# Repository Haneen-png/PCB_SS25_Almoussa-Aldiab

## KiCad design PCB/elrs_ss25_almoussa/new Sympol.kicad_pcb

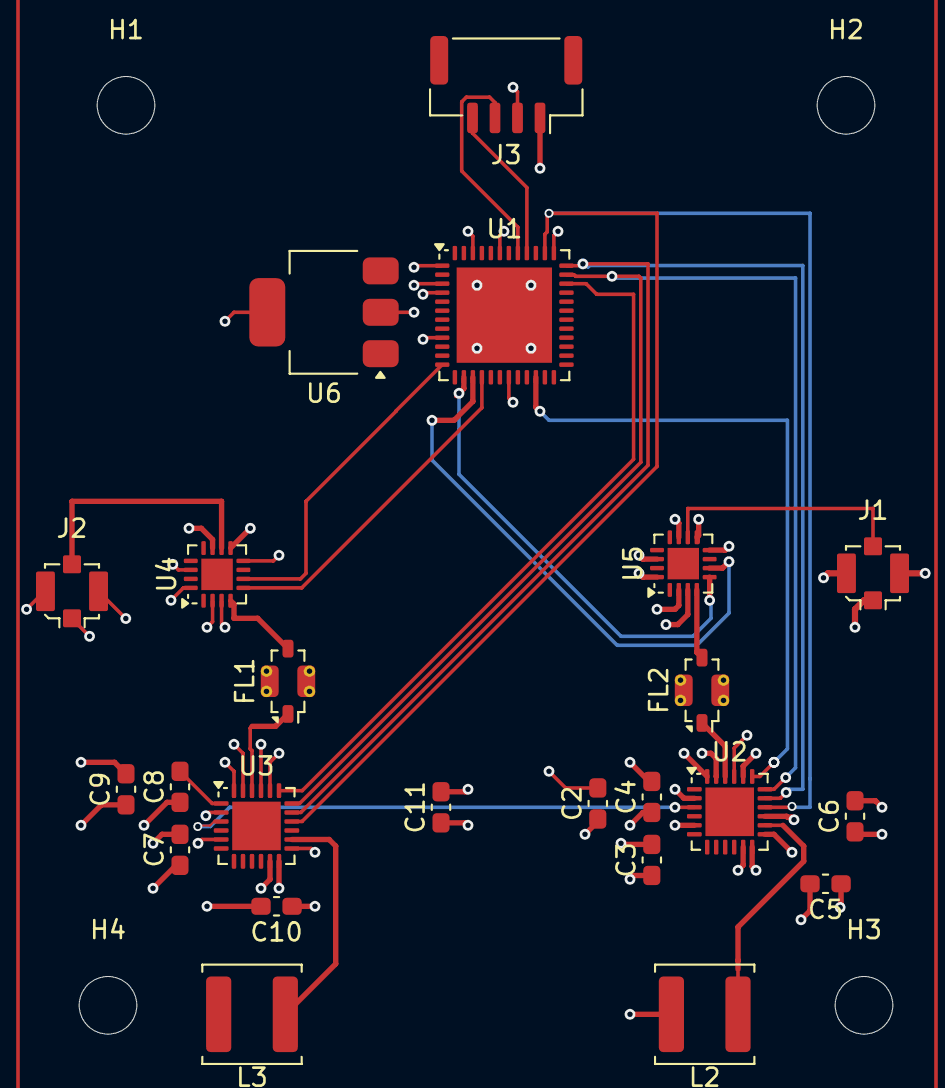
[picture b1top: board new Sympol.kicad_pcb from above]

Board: 4 copper layers, 27 parts (0 on the bottom side), 19 nets.

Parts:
C2, C3, C7, C8: 10nF; C_0603_1608Metric_Pad1.08x0.95mm_HandSolder
C4, C9: 470nF; C_0603_1608Metric_Pad1.08x0.95mm_HandSolder
C5, C6, C10, C11: 100nF; C_0603_1608Metric_Pad1.08x0.95mm_HandSolder
FL1, FL2: BFCN-2450; Filter_Mini-Circuits_FV1206-4
H1, H2, H3, H4: MountingHole; MountingHole_3.2mm_M3
J1, J2: Conn_Coaxial; U.FL_Molex_MCRF_73412-0110_Vertical
J3: Conn_01x04_Pin; JST_GH_SM04B-GHS-TB_1x04-1MP_P1.25mm_Horizontal
L2, L3: 15uH KPL-SE9040-150; L_APV_ANR5045
U1: ESP32-PICO-D4; QFN-48-1EP_7x7mm_P0.5mm_EP5.3x5.3mm
U2, U3: QFN-24-1EP_4x4mm_P0.5mm_EP2.7x2.7mm
U4: U6; QFN-16-1EP_3x3mm_P0.5mm_EP1.75x1.75mm
U5: QFN-16-1EP_3x3mm_P0.5mm_EP1.75x1.75mm
U6: SOT-223-3_TabPin2

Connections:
+3.3V: C3.2, C4.1, C5.1, C6.1, C7.2, C9.1, C10.1, C11.1, L2.2, L3.2, U1.1 (VDDA), U1.3 (VDDA3P3), U1.4 (VDDA3P3), U1.9 (EN), U1.19 (VDD3P3_RTC), U1.37 (VDD3P3_CPU), U1.43 (VDDA), U1.46 (VDDA), U2.2 (VDD_IN), U2.11 (VBAT_ID), U2.12 (DCC_FB), U2.15 (VBAT), U3.2 (VDD_IN), U3.11 (VBAT_ID), U3.12 (DCC_FB), U3.15 (VBAT), U4.2 (VO), U5.14 (VDD), U5.16 (VDD)
/CS0: U1.22 (IO2), U2.19 (NSS_CTS)
/CS1: U1.34 (IO5), U3.19 (NSS_CTS)
/MISO: U1.38 (IO19), U2.16 (MISO_IX), U3.16 (MISO_IX)
/MOSI: U1.36 (IO23), U2.17 (MOSI_RX), U3.17 (MOSI_RX)
/NRESET: U2.3 (NRESET), U3.3 (NRESET)
/RX: J3.4, U1.40 (U0RXD/IO3)
/RXEN0: U1.15 (IO26), U5.6 (RXEN)
/SCK: U1.35 (IO18), U2.18 (SCK_RTSN), U3.18 (SCK_RTSN)
/TX: J3.3, U1.41 (U0TXD/IO1)
GND: C2.1, C3.1, C4.2, C5.2, C6.2, C7.1, C8.1, C9.2, C10.2, C11.2, FL1.1 (IN), FL2.1 (IN), J2.1 (In), J3.1, U1.49 (GND), U2.5 (GND), U2.13 (GND), U2.20 (GND), U2.21 (GNO), U2.22 (RFIO), U2.23 (GND), U2.24 (GNO), U3.5 (GND), U3.13 (GND), U3.20 (GND), U3.21 (GNO), U3.22 (RFIO), U3.23 (GND), U3.24 (GNO), U4.1 (GND), U5.2 (GND), U5.3 (GND), U5.8 (GND), U5.9 (GND), U5.11 (GND), U6.2 (GND), U6.3 (GND)
unnamed: FL1.2 (GND), FL1.4 (GND)
unnamed: FL2.2 (GND), FL2.4 (GND)
unnamed: FL2.3 (OUT), U5.4 (TXRX)
unnamed: J1.1 (In), U5.10 (ANT)
unnamed: L2.1, U2.14 (DCC_SW)
unnamed: C2.2, U2.1 (VR_PA)
unnamed: L3.1, U3.14 (DCC_SW)
unnamed: C8.2, U3.1 (VR_PA)

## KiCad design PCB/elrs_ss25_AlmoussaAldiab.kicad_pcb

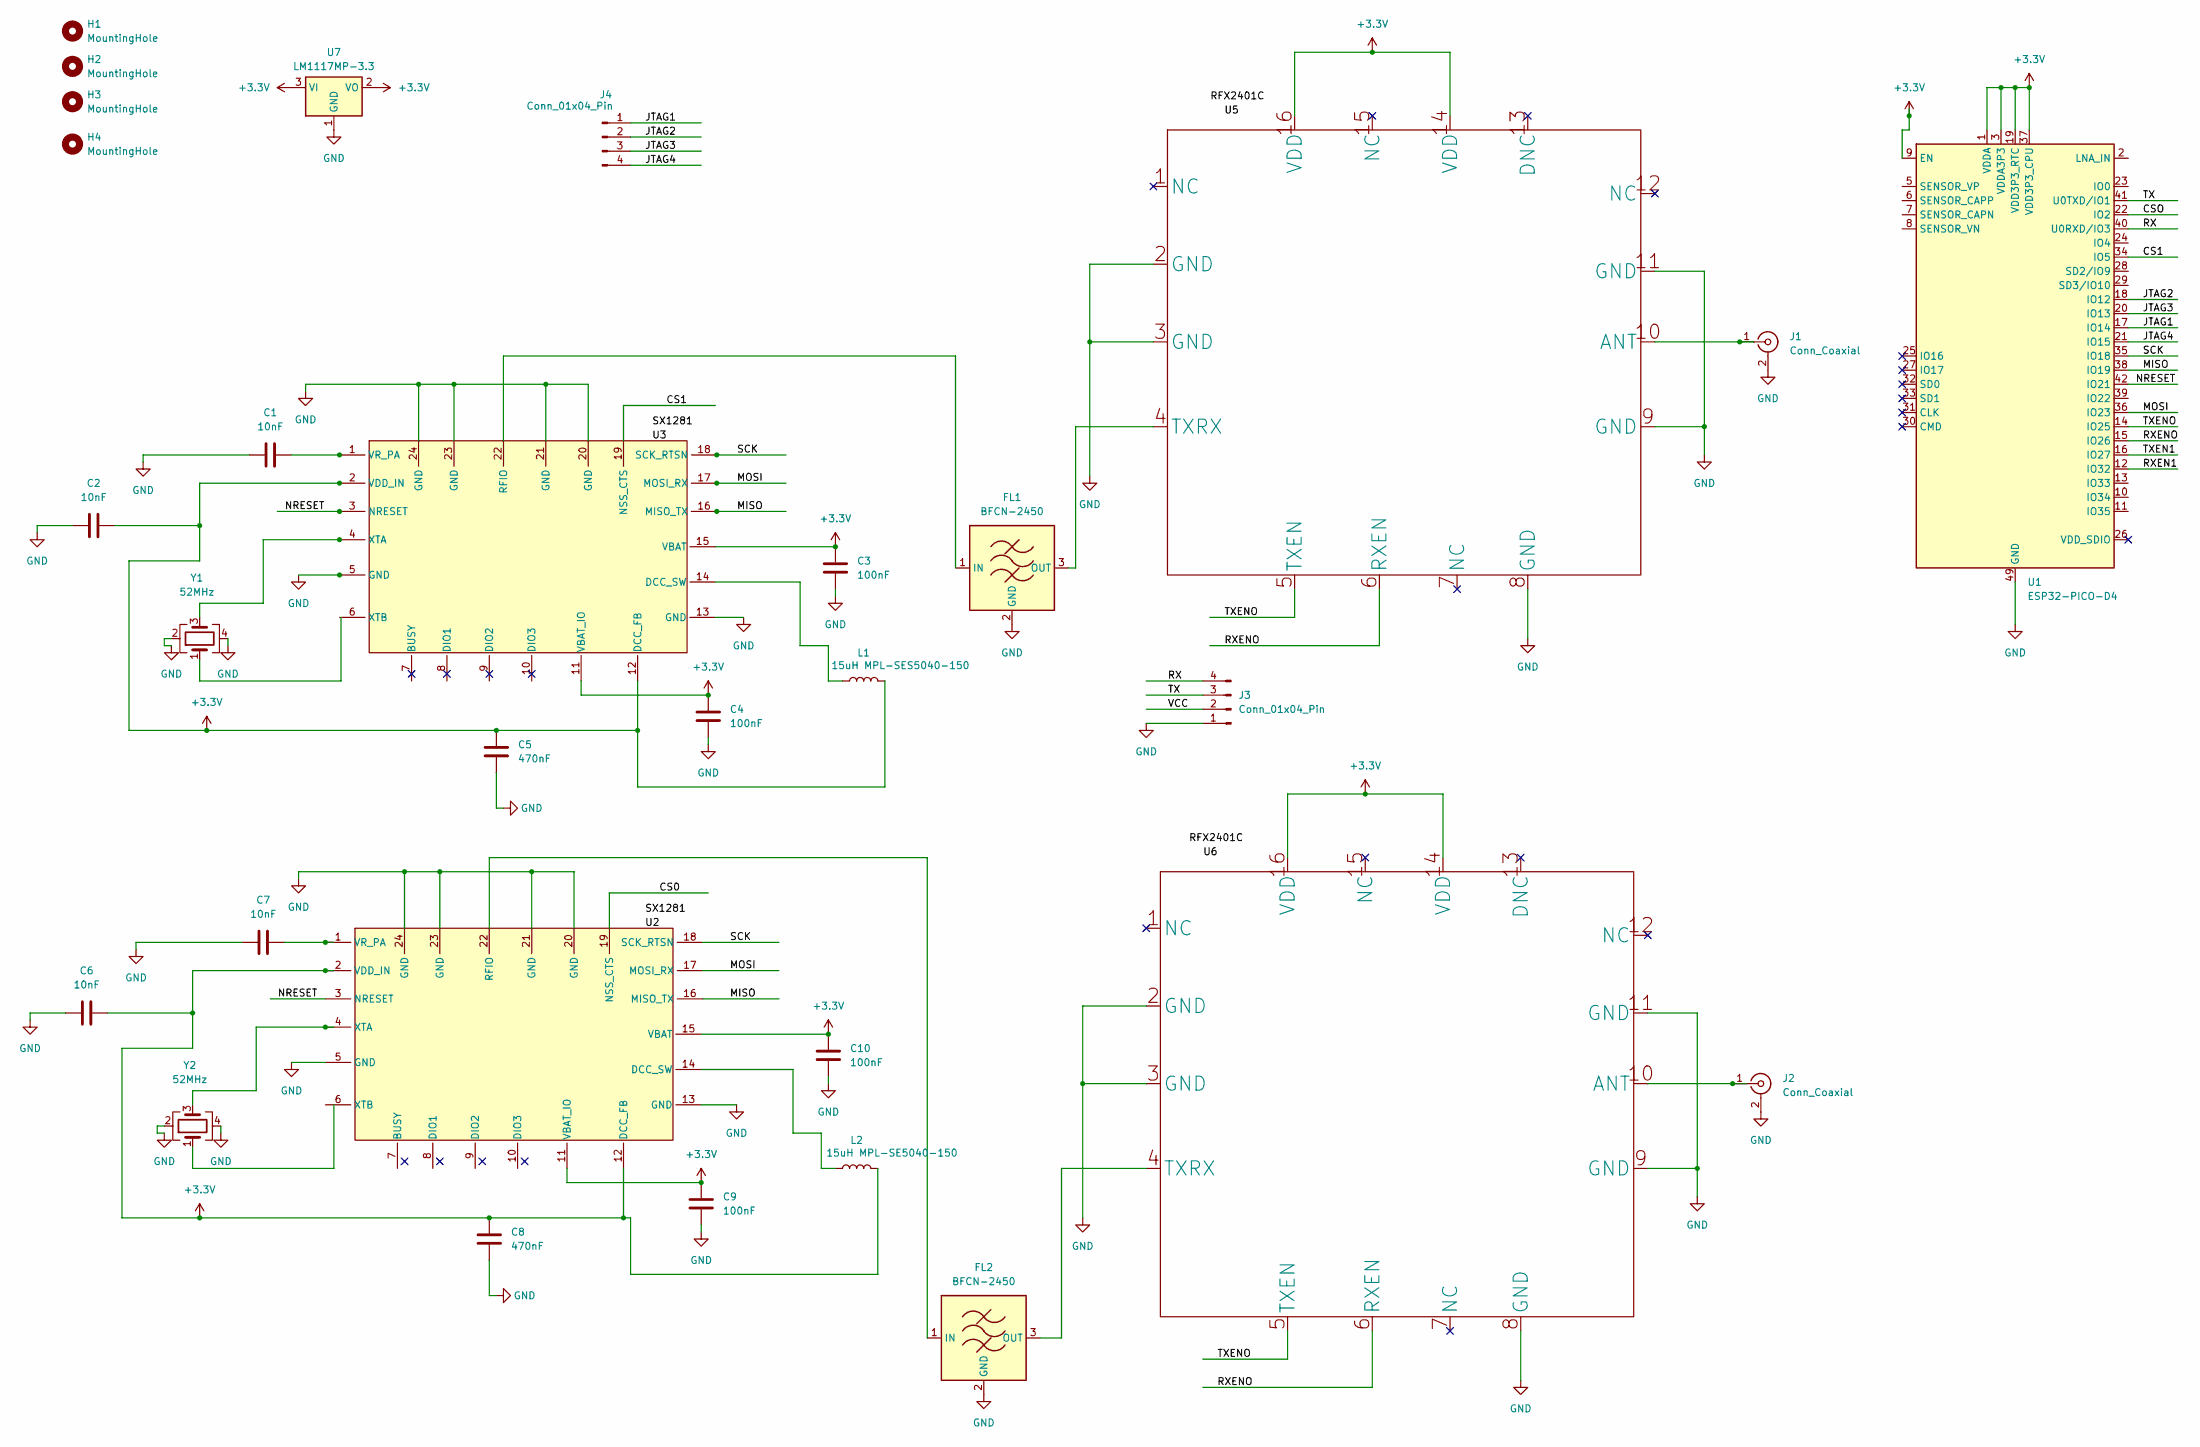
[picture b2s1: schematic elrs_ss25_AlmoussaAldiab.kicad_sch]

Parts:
C1, C2, C6, C7: 10nF; C_0603_1608Metric_Pad1.08x0.95mm_HandSolder
C3, C4, C9, C10: 100nF; C_0603_1608Metric_Pad1.08x0.95mm_HandSolder
C5, C8: 470nF; C_0603_1608Metric_Pad1.08x0.95mm_HandSolder
FL1, FL2: BFCN-2450; Filter_Mini-Circuits_FV1206-4
H1, H2, H3, H4: MountingHole; MountingHole_3.2mm_M3
J1, J2: Conn_Coaxial; U.FL_Molex_MCRF_73412-0110_Vertical
J3: Conn_01x04_Pin; JST_GH_SM04B-GHS-TB_1x04-1MP_P1.25mm_Horizontal
J4: Conn_01x04_Pin; PinSocket_1x04_P2.54mm_Vertical
L1: 15uH MPL-SES5040-150; L_APV_ANR5045
L2: 15uH MPL-SE5040-150; L_APV_ANR5045
U1: ESP32-PICO-D4; QFN-48-1EP_7x7mm_P0.5mm_EP5.3x5.3mm
U2, U3: QFN-24-1EP_4x4mm_P0.5mm_EP2.7x2.7mm
U4, U6: QFN-16-1EP_3x3mm_P0.5mm_EP1.75x1.75mm
U7: LM1117MP-3.3; SOT-223-3_TabPin2
Y1, Y2: 52MHz

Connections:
/CS0: U3.19 (NSS_CTS)
/CS1: U1.34 (IO5), U2.19 (NSS_CTS)
/CSO: U1.22 (IO2)
/JTAG1: J4.1, U1.17 (IO14)
/JTAG2: J4.2, U1.18 (IO12)
/JTAG3: J4.3, U1.20 (IO13)
/JTAG4: J4.4, U1.21 (IO15)
/MISO: U1.38 (IO19), U2.16 (MISO_TX), U3.16 (MISO_TX)
/MOSI: U1.36 (IO23), U2.17 (MOSI_RX), U3.17 (MOSI_RX)
/NRESET: U1.42 (IO21), U2.3 (NRESET), U3.3 (NRESET)
/RX: J3.4, U1.40 (U0RXD/IO3)
/RXEN1: U1.12 (IO32)
/RXENO: U1.15 (IO26), U4.6 (RXEN), U6.6 (RXEN)
/SCK: U1.35 (IO18), U2.18 (SCK_RTSN), U3.18 (SCK_RTSN)
/TX: J3.3, U1.41 (U0TXD/IO1)
/TXEN1: U1.16 (IO27)
/TXENO: U1.14 (IO25), U4.5 (TXEN), U6.5 (TXEN)
GND: C1.1, C2.1, C3.1, C4.1, C5.2, C6.1, C7.1, C8.2, C9.1, C10.1, FL1.2 (GND), FL1.4 (GND), FL2.2 (GND), FL2.4 (GND), J1.2 (Ext), J2.2 (Ext), J3.1, U1.49 (GND), U2.5 (GND), U2.13 (GND), U2.20 (GND), U2.21 (GND), U2.23 (GND), U2.24 (GND), U3.5 (GND), U3.13 (GND), U3.20 (GND), U3.21 (GND), U3.23 (GND), U3.24 (GND), U4.2 (GND), U4.3 (GND), U4.8 (GND), U4.9 (GND), U4.11 (GND), U6.2 (GND), U6.3 (GND), U6.8 (GND), U6.9 (GND), U6.11 (GND), U7.1 (GND), Y1.2, Y1.4, Y2.2, Y2.4
unnamed: FL1.1 (IN), U2.22 (RFIO)
unnamed: FL1.3 (OUT), U4.4 (TXRX)
unnamed: FL2.1 (IN), U3.22 (RFIO)
unnamed: FL2.3 (OUT), U6.4 (TXRX)
unnamed: J1.1 (In), U4.10 (ANT)
unnamed: J2.1 (In), U6.10 (ANT)
unnamed: L1.1, U2.14 (DCC_SW)
unnamed: C1.2, U2.1 (VR_PA)
unnamed: U2.4 (XTA), Y1.3
unnamed: L2.1, U3.14 (DCC_SW)
unnamed: C7.2, U3.1 (VR_PA)
unnamed: U3.4 (XTA), Y2.3

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
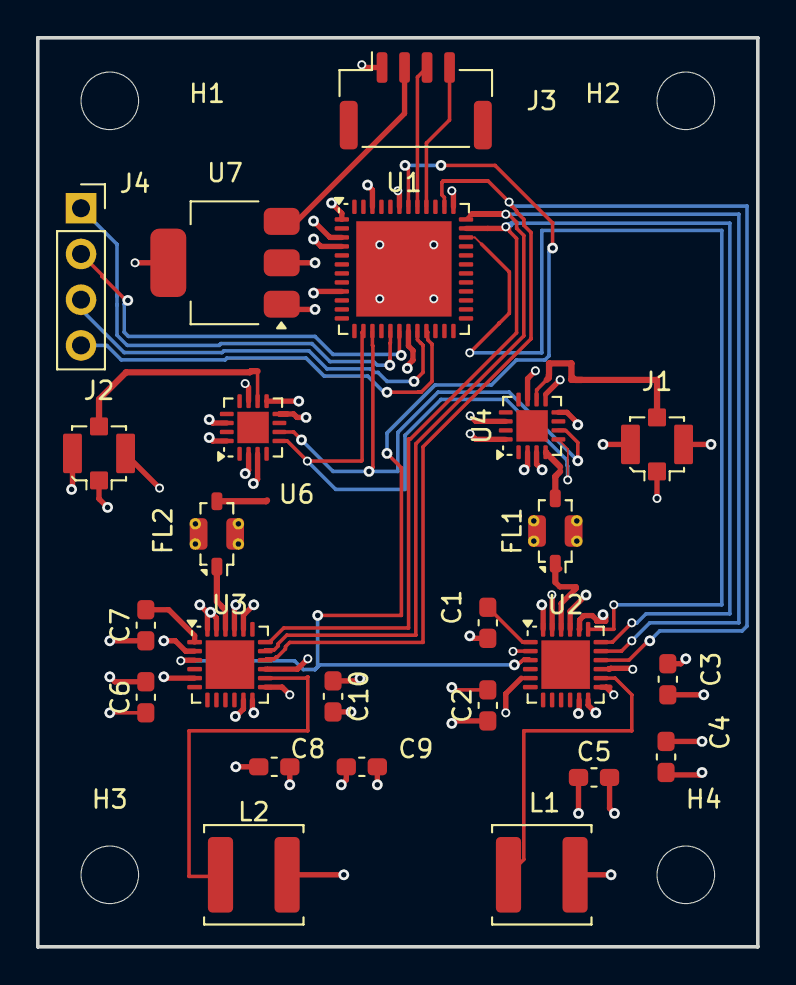
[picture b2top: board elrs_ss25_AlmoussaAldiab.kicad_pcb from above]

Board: 4 copper layers, 40.0 x 50.5 mm, 28 parts (0 on the bottom side), 26 nets.

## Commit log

2025-04-10 Haneen
2025-06-18 Create PCB
2025-06-18 Create Dokumentation
2025-06-18 Create Datenblätter
2025-06-18 Create Dokumentation2
2025-06-18 Create Beispiel
